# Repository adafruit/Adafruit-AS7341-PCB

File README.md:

## Adafruit AS7341 10-Channel Light / Color Breakout PCB

<a href="http://www.adafruit.com/products/4698"><br/>
Click here to purchase one from the Adafruit shop</a>

PCB files for the Adafruit AS7341 10-Channel Light / Color Breakout. 

Format is EagleCAD schematic and board layout
* https://www.adafruit.com/product/4698

### Description

INSERT PRODUCT COPY HERE
The AS7341 by AMS is a 11/10 channel spectrometer which is a special type of light sensor that is able to detect not only the amount of light present, but also the amounts of light within different wavelengths. This means that you can use it to detect, much better than the human eye is capable of, what color or colors of light is present. The AS7341 packs within its 3x2mm footprint 16 different sensors that can detect 8 separate, overlapping bands of colored light. As if that weren't enough, it also includes sensors for white light as well as Near Infra-red light, and even sensors made specifically for detecting light flicker at specific frequencies from things like indoor lighting.

The super-human color measuring capabilities of the AS7341 can be used to quantify the specific makeup of whatever interesting colors you can point it at, and can do so with more accuracy and specificity than a well trained artist. Now you don't need to go to art school to tell Pavo from Smalt, instead you can have the AS7341 can give you a clue how blue your blue is. This is possible thanks to the impressive collection of sensors in the AS7341 being routed through a 16-bit 6-channel ADC that takes the raw measurements and converts them to digital values that can be read out over I2C.

11 readable individual sensor elements don’t exactly fit through a 6-channel ADC all at once, so the chip includes a so-called Super MUX (SMUX) that allows you to route the signal from any sensor to any ADC channel. Now that’s some super multiplexing! The sensor also has GPIO and interrupt pins that can allow it to communicate directly with other sensors, or the microcontroller itself.

All of this capability is made accessible by mounting the sensor on a Stemma QT form factor breakout board, complete with level shifting circuitry and Sparkfun Qwiic compatible Stemma QT connectors. This means that you can, without needing to solder, connect our AS7341 breakout into your 3.3V or 5V microcontroller of choice be it an Arduino Uno, Raspberry Pi, or one of the many . While it certainly takes a bit of work to make all those different light sensors share their measurements, our Arduino and CircuitPython libraries take care of all of that hard work for you, and even include example code to help get you started. Read on and you'll find library installation instructions, as well as wiring diagrams that make using the AS7341 super easy.

### License

Adafruit invests time and resources providing this open source design, please support Adafruit and open-source hardware by purchasing products from [Adafruit](https://www.adafruit.com)!

Designed by Limor Fried/Ladyada for Adafruit Industries.

Creative Commons Attribution/Share-Alike, all text above must be included in any redistribution. 
See license.txt for additional details.

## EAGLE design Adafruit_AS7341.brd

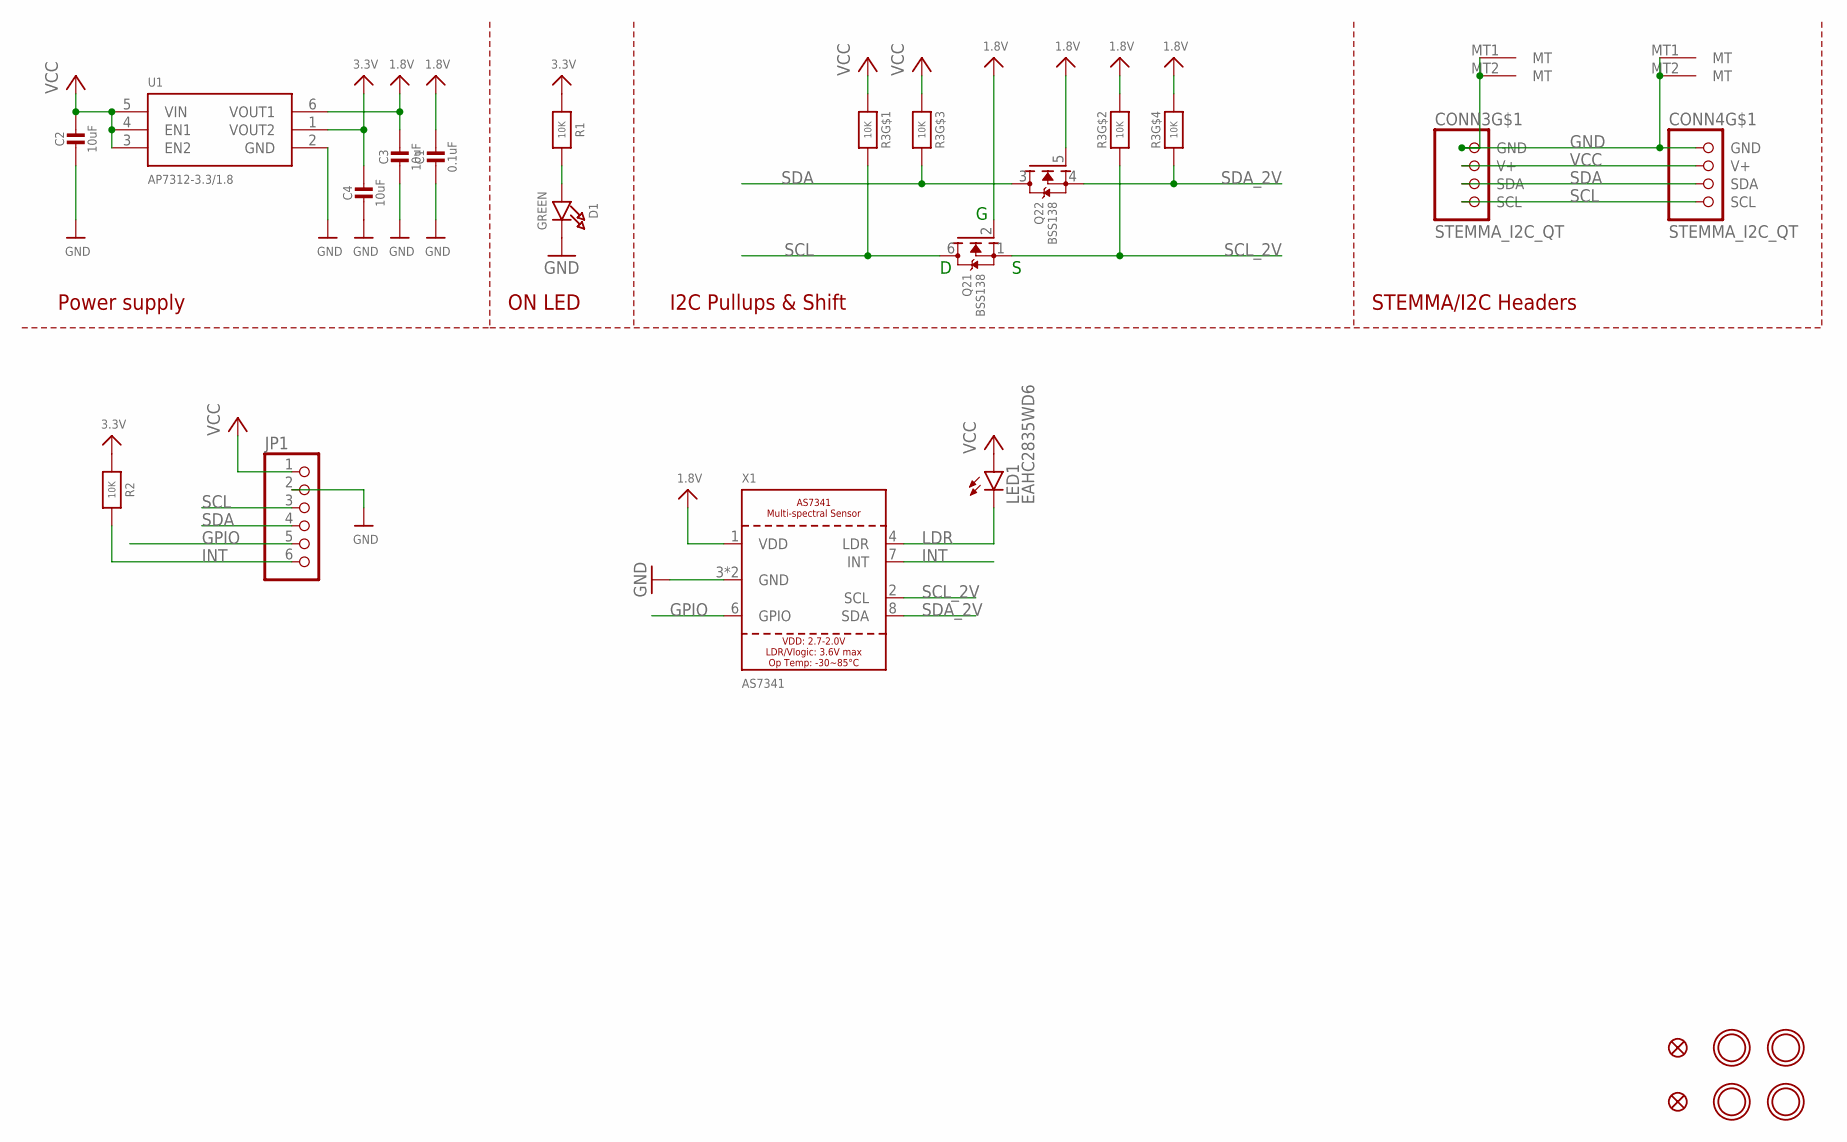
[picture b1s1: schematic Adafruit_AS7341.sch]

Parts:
C1: 0.1uF; 0603-NO
C2, C3, C4: 10uF; 0805-NO
CONN3, CONN4: STEMMA_I2C_QT; JST_SH4
D1: GREEN; CHIPLED_0603_NOOUTLINE
FID3, FID4: FIDUCIAL_1MM
JP1: HEADER-1X670MIL; 1X06_ROUND_70
LED1: EAHC2835WD6; KA-3528ASYC
Q2: BSS138; SOT363
R1, R2: 10K; 0603-NO
R3: 10K; RESPACK_4X0603
U1: AP7312-3.3/1.8; SOT23-6
U$1, U$17, U$19, U$21: MOUNTINGHOLE2.5; MOUNTINGHOLE_2.5_PLATED
X1: AS7341

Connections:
1.8V: C1.1, C3.1, Q2.2 (G), Q2.5 (G), R3.2 (1), R3.4 (1), U1.6 (VOUT1), X1.1 (VDD)
3.3V: C4.1, R1.1, R2.1, U1.1 (VOUT2)
GND: C1.2, C2.2, C3.2, C4.2, CONN3.1 (GND), CONN3.MT1 (MT), CONN3.MT2 (MT), CONN4.1 (GND), CONN4.MT1 (MT), CONN4.MT2 (MT), D1.C, JP1.2, U1.2 (GND), X1.3 (GND), X1.5 (GND)
GPIO: JP1.5, X1.6 (GPIO)
INT: JP1.6, R2.2, X1.7 (INT)
LDR: LED1.C, X1.4 (LDR)
unnamed: D1.A, R1.2
SCL: CONN3.4 (SCL), CONN4.4 (SCL), JP1.3, Q2.6 (D), R3.8 (2)
SCL_2V: Q2.1 (S), R3.7 (2), X1.2 (SCL)
SDA: CONN3.3 (SDA), CONN4.3 (SDA), JP1.4, Q2.3 (D), R3.6 (2)
SDA_2V: Q2.4 (S), R3.5 (2), X1.8 (SDA)
VCC: C2.1, CONN3.2 (V+), CONN4.2 (V+), JP1.1, LED1.A, R3.1, R3.3 (1), U1.3 (EN2), U1.4 (EN1), U1.5 (VIN)

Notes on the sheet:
I2C Pullups & Shift
STEMMA/I2C Headers
ON LED
Power supply

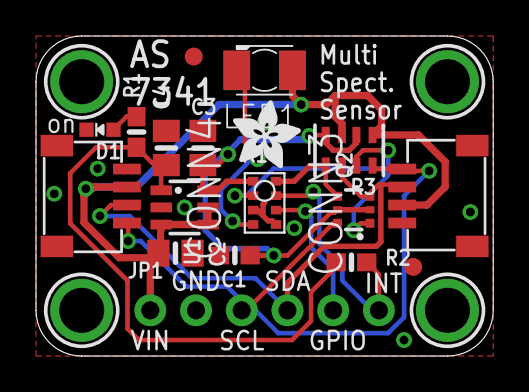
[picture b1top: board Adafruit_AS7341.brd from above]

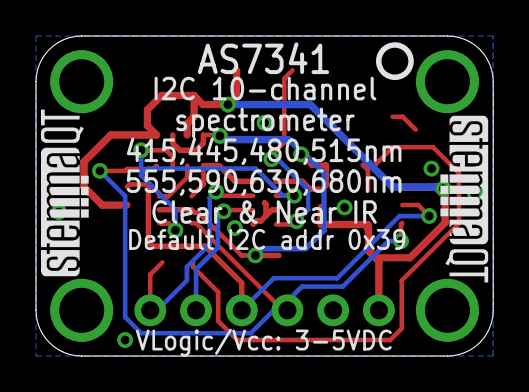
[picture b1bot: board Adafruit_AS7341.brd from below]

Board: 2 copper layers, 25.4 x 17.8 mm, 25 parts (3 on the bottom side), 12 nets.

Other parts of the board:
U$22: ADAFRUIT_3.5MM
U$25: PCBFEAT-REV-040
U$30, U$31: STEMMAQT

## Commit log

2020-08-13 updating image

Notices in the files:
parts and their libraries:
microbuilder: This work is placed in the public domain, and may be freely used for commercial and non-commercial work with the following conditions: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
